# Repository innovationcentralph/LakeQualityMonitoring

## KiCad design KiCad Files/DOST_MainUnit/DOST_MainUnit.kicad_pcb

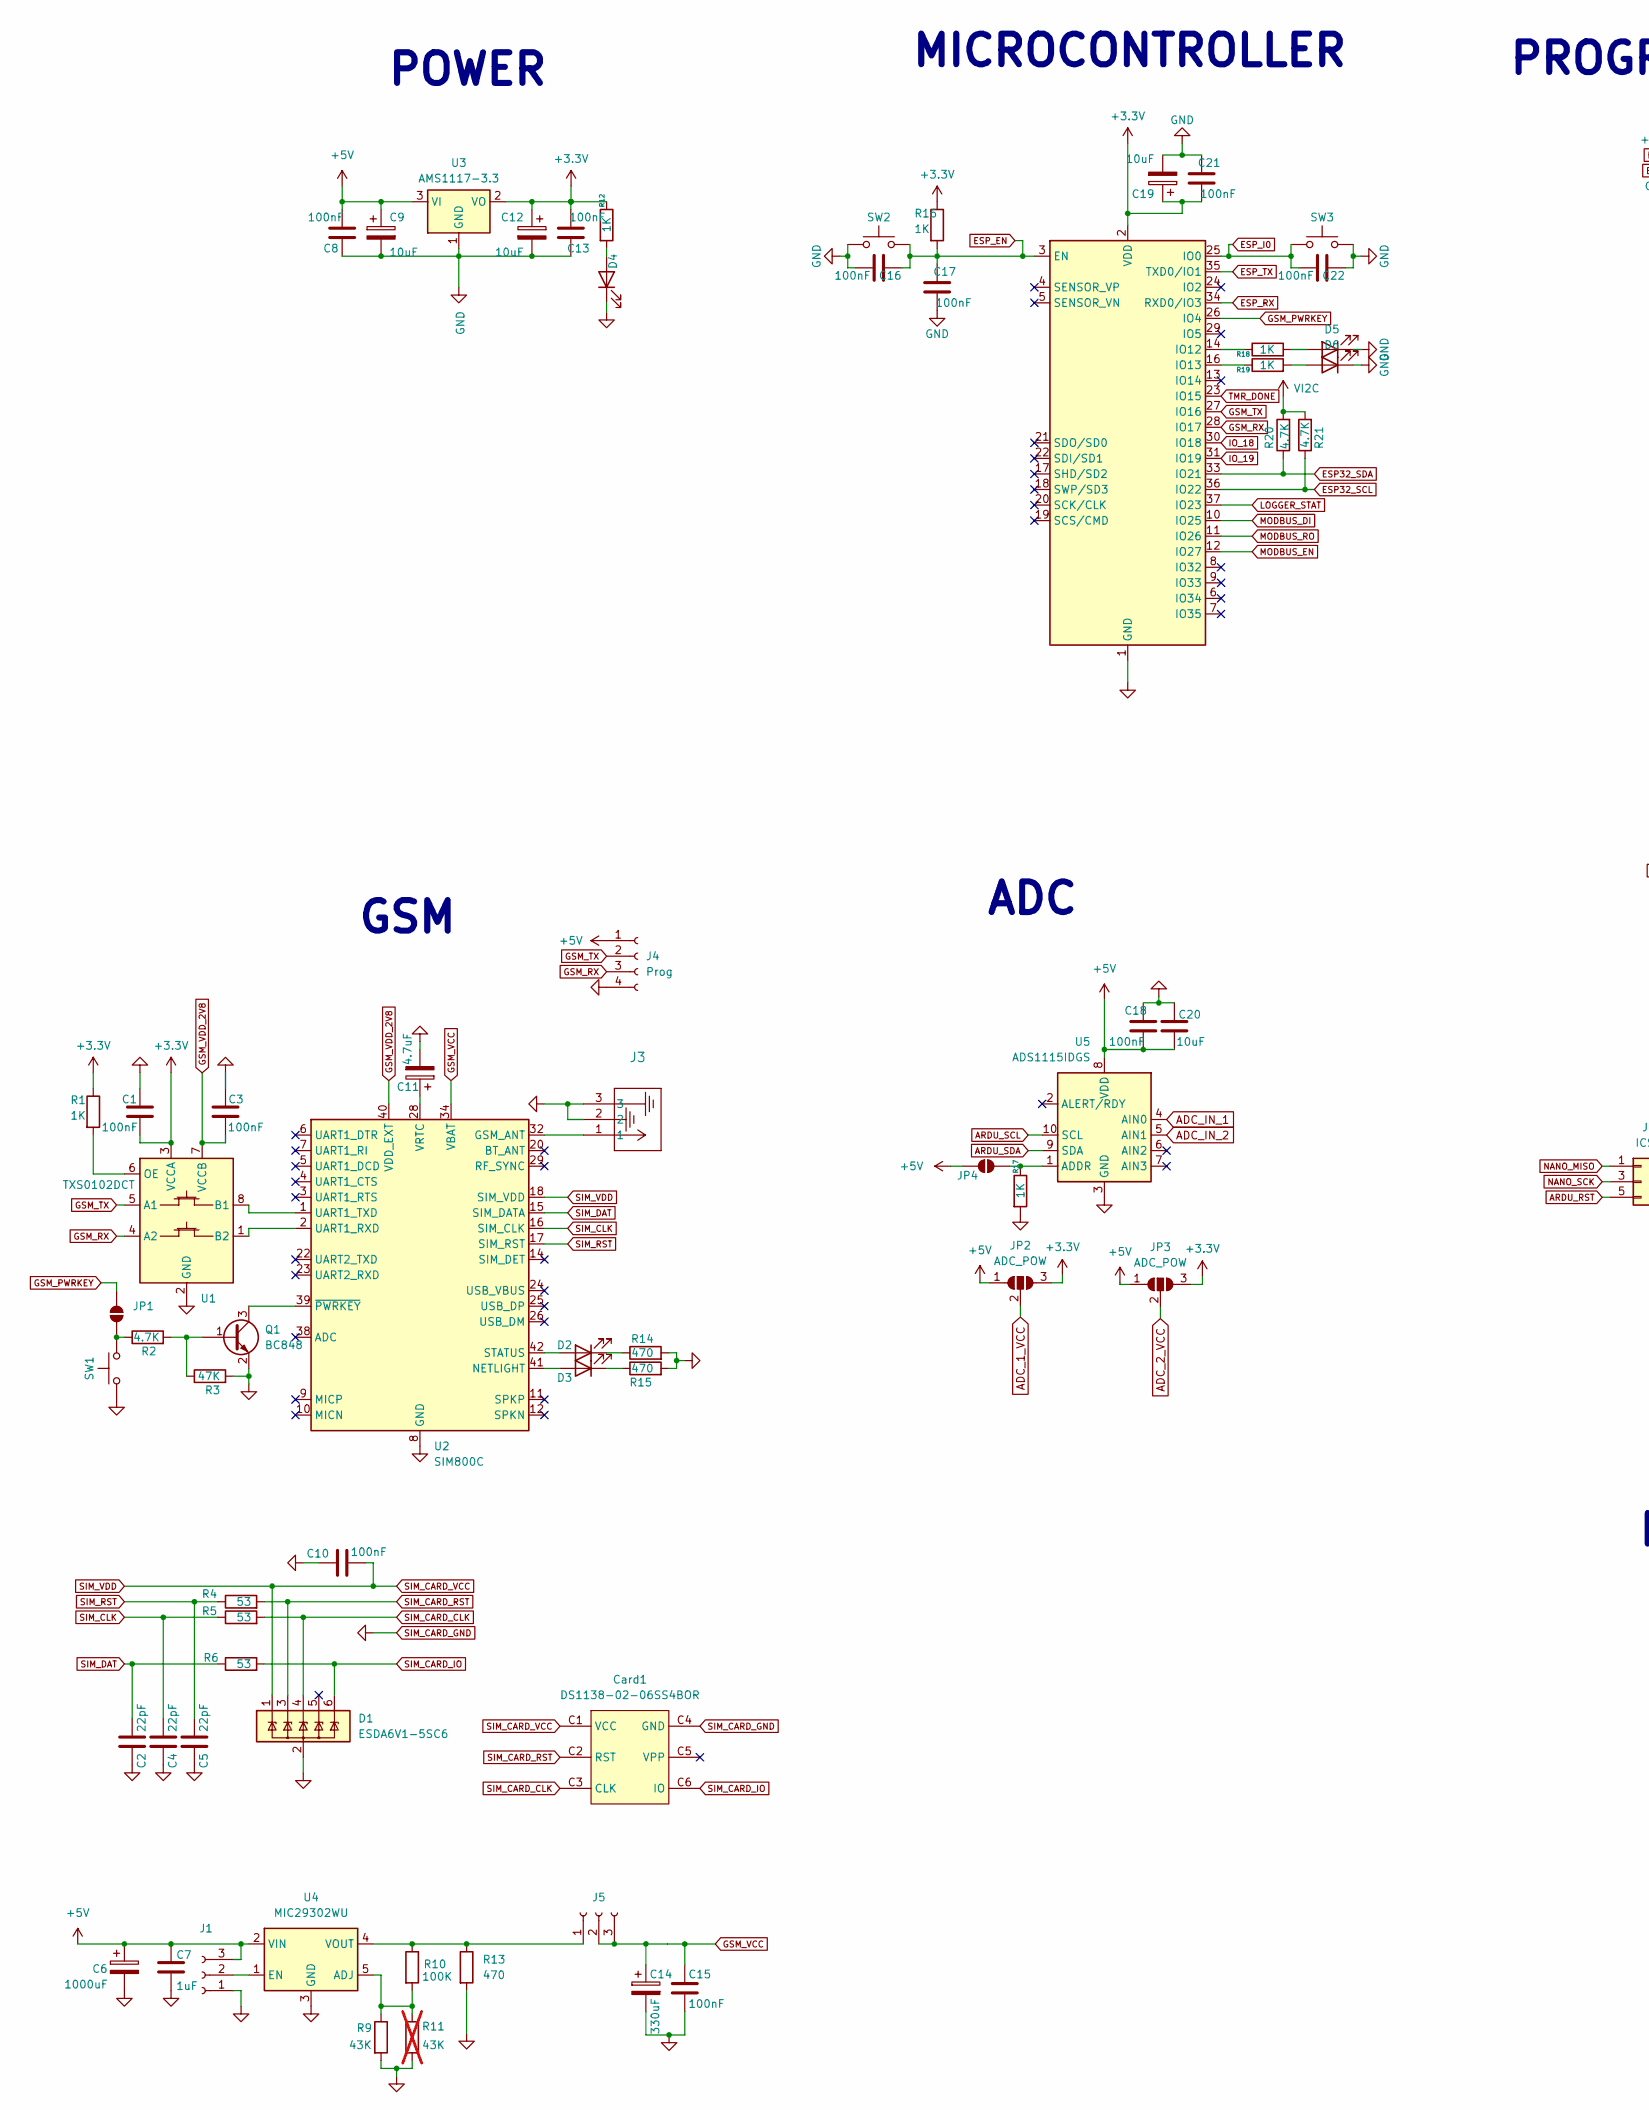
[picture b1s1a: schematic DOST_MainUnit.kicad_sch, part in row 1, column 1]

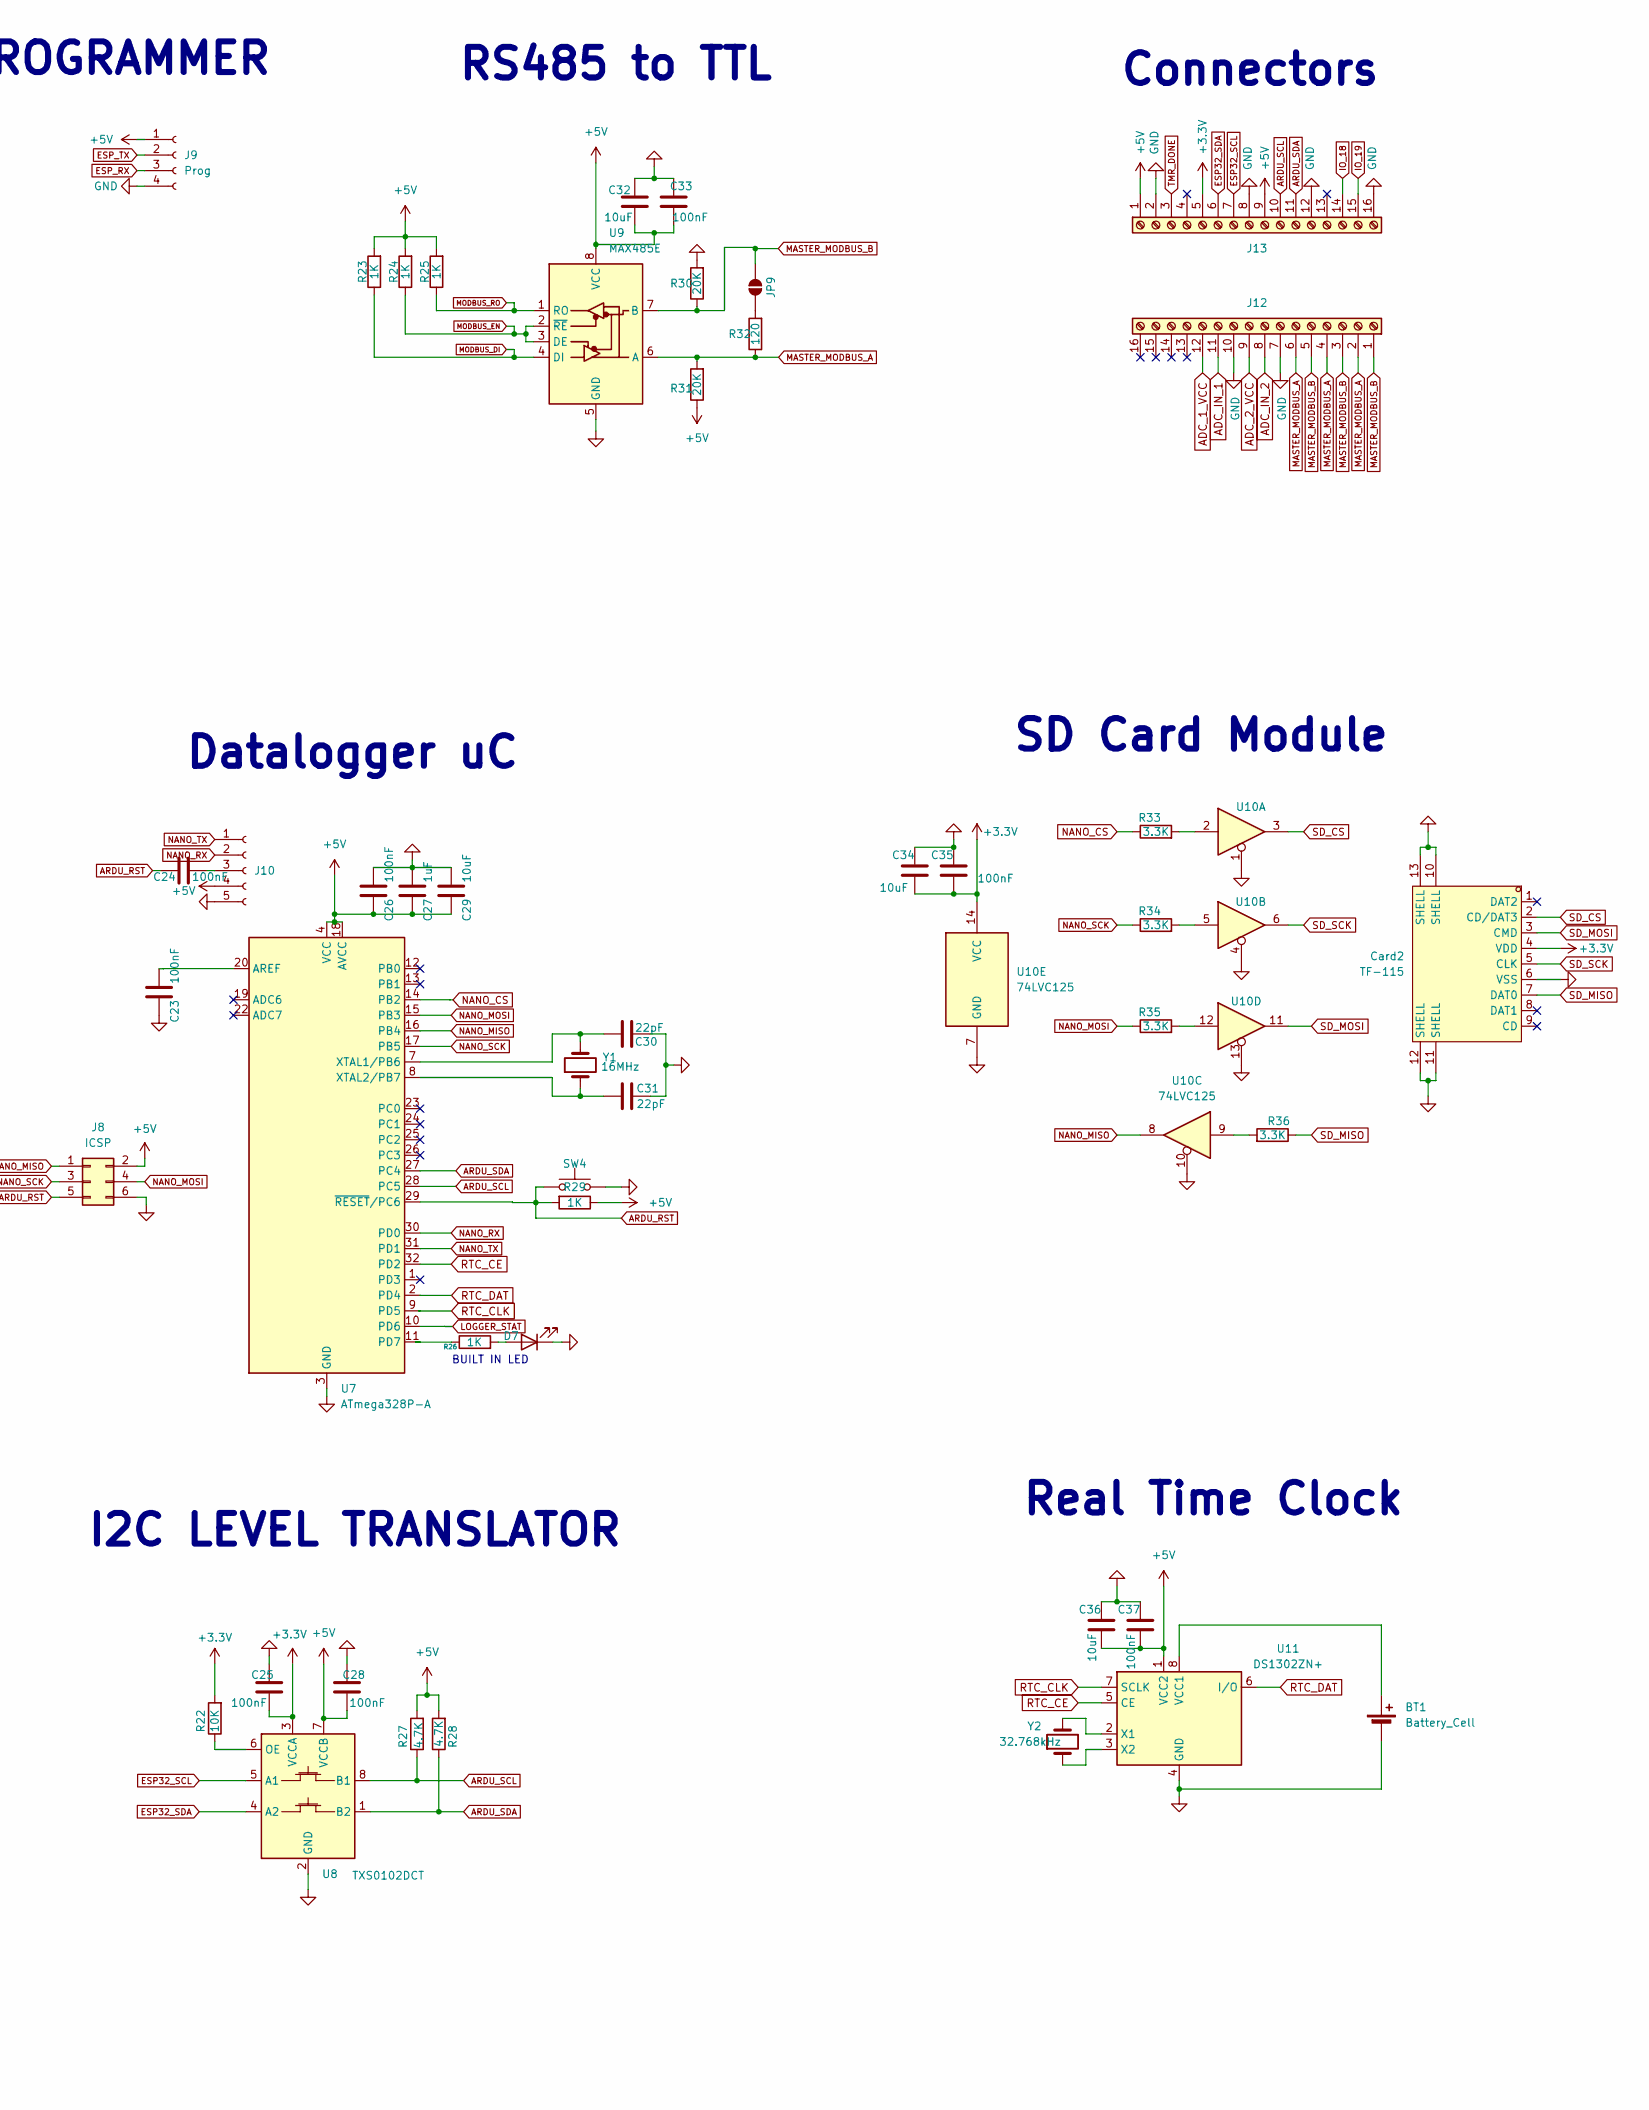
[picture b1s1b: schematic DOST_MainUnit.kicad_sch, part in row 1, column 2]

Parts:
BT1: Battery_Cell; BAT-TH_CR2032-BS-6-1; LCSC C70377
C1, C3, C25, C28: 100nF; C_0805_2012Metric_Pad1.18x1.45mm_HandSolder; LCSC C1546
C2, C4, C5: 22pF; C_0805_2012Metric_Pad1.18x1.45mm_HandSolder
C6: 1000uF; CP_Elec_10x10.5
C7: 1uF; C_0805_2012Metric_Pad1.18x1.45mm_HandSolder
C8, C13, C16, C17, C18, C21, C22, C23, C24, C26, C33, C35, C37: 100nF; C_0805_2012Metric_Pad1.18x1.45mm_HandSolder; LCSC C60474
C9, C12, C19, C32: 10uF; C_0805_2012Metric_Pad1.18x1.45mm_HandSolder; LCSC C15850
C10, C15: 100nF; C_0805_2012Metric_Pad1.18x1.45mm_HandSolder
C11: 4.7uF; CP_EIA-3528-12_Kemet-T_Pad1.50x2.35mm_HandSolder
C14: 330uF; CP_EIA-7343-31_Kemet-D_Pad2.25x2.55mm_HandSolder
C20, C29, C34, C36: 10uF; C_0805_2012Metric_Pad1.18x1.45mm_HandSolder; LCSC C96446
C27: 1uF; C_0805_2012Metric_Pad1.18x1.45mm_HandSolder; LCSC C52923
C30, C31: 22pF; C_0805_2012Metric_Pad1.18x1.45mm_HandSolder; LCSC C96446
Card1: DS1138-02-06SS4BOR; SIM-SMD_DS1138-02-06SS4BOR; LCSC Part C91413
Card2: TF-115; TF-SMD_TF-115; LCSC C266620
D1: ESDA6V1-5SC6; SOT-23-6
D2, D3: LED; LED_0805_2012Metric_Pad1.15x1.40mm_HandSolder
D4, D5, D6, D7: LED; LED_0805_2012Metric_Pad1.15x1.40mm_HandSolder; LCSC C2297
J1, J5: Conn_01x03_Socket; PinHeader_1x03_P2.54mm_Vertical
J3: CONUFL001-SMD-T; CONN1_CONUFL_TEC
J4, J9: Prog; PinHeader_1x04_P2.54mm_Vertical
J8: ICSP; PinHeader_2x03_P2.54mm_Vertical_SMD
J10: Conn_01x05_Socket; PinHeader_1x05_P2.54mm_Vertical
J12, J13: Screw_Terminal_01x16; TerminalBlock_Phoenix_MKDS-1,5-16-5.08_1x16_P5.08mm_Horizon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
JP1, JP4, JP9: SolderJumper_2_Open; SolderJumper-2_P1.3mm_Open_Pad1.0x1.5mm
JP2, JP3: ADC_POW; SolderJumper-3_P1.3mm_Open_Pad1.0x1.5mm
Q1: BC848; SOT-23
R1, R12, R16, R17, R18, R19, R23, R24, R25, R26, R29: 1K; R_0603_1608Metric_Pad0.98x0.95mm_HandSolder; LCSC C21190
R2: 4.7K; R_0603_1608Metric_Pad0.98x0.95mm_HandSolder
R3: 47K; R_0805_2012Metric_Pad1.20x1.40mm_HandSolder
R4, R5, R6: 53; R_0805_2012Metric_Pad1.20x1.40mm_HandSolder
R9: 43K; R_0805_2012Metric_Pad1.20x1.40mm_HandSolder
R10: 100K; R_0805_2012Metric_Pad1.20x1.40mm_HandSolder
R11: 43K; R_0805_2012Metric_Pad1.20x1.40mm_HandSolder; not fitted
R13, R14, R15: 470; R_0805_2012Metric_Pad1.20x1.40mm_HandSolder
R20, R21, R27, R28: 4.7K; R_0603_1608Metric_Pad0.98x0.95mm_HandSolder; LCSC C23162
R22: 10K; R_0603_1608Metric_Pad0.98x0.95mm_HandSolder; LCSC C25804
R30, R31: 20K; R_0805_2012Metric_Pad1.20x1.40mm_HandSolder; LCSC C163978
R32: 120; R_0805_2012Metric_Pad1.20x1.40mm_HandSolder; LCSC C2907224
R33, R34, R35, R36: 3.3K; R_0603_1608Metric_Pad0.98x0.95mm_HandSolder; LCSC C22978
SW1, SW2, SW3, SW4: SW_Push; SW_SPST_CK_RS282G05A3; LCSC C2689642
U1, U8: TXS0102DCT; SSOP-8_2.95x2.8mm_P0.65mm
U2: SIM800C; SIMCom_SIM800C
U3: AMS1117-3.3; SOT-223-3_TabPin2
U4: MIC29302WU; TO-263-5_TabPin3
U5: ADS1115IDGS; VSSOP-10_3x3mm_P0.5mm; LCSC C37593
U6: ESP32-WROOM-32; LCSC C529577
U7: ATmega328P-A; TQFP-32_7x7mm_P0.8mm; LCSC C14877
U9: MAX485E; SOP-8_3.9x4.9mm_P1.27mm; LCSC C481667
U10: 74LVC125; TSSOP-14_L5.0-W4.4-P0.65-LS6.4-BL; LCSC C6059
U11: DS1302ZN+; SOIC-8_3.9x4.9mm_P1.27mm; LCSC C14334
Y1: 16MHz; Crystal_HC49-4H_Vertical
Y2: 32.768kHz; Crystal_C38-LF_D3.0mm_L8.0mm_Vertical; LCSC C97606

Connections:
+3.3V: C1.2, C12.1, C13.1, C19.1, C21.1, C25.2, C34.1, C35.1, Card2.4 (VDD), J13.5, JP2.3 (B), JP3.3 (B), R1.1, R12.1, R16.1, R22.2, U1.3 (VCCA), U3.2 (VO), U6.2 (VDD), U8.3 (VCCA), U10.14 (VCC)
+5V: C6.1, C7.1, C8.1, C9.1, C18.1, C20.2, C26.2, C27.2, C28.2, C29.2, C32.2, C33.1, C36.1, C37.1, J1.3, J4.1, J8.2, J9.1, J10.4, J13.1, J13.9, JP2.1 (A), JP3.1 (A), JP4.2 (B), R23.2, R24.2, R25.2, R27.2, R28.2, R29.1, R31.1, U3.3 (VI), U4.2 (VIN), U5.8 (VDD), U7.4 (VCC), U7.6 (VCC), U7.18 (AVCC), U8.7 (VCCB), U9.8 (VCC), U11.1 (VCC2)
ADC_1_VCC: J12.12, JP2.2 (C)
ADC_2_VCC: J12.9, JP3.2 (C)
ADC_IN_1: J12.11, U5.4 (AIN0)
ADC_IN_2: J12.8, U5.5 (AIN1)
ARDU_RST: C24.2, J8.5, R29.2, SW4.1, U7.29 (~RESET/PC6)
ARDU_SCL: J13.10, R27.1, U5.10 (SCL), U7.28 (PC5), U8.8 (B1)
ARDU_SDA: J13.11, R28.1, U5.9 (SDA), U7.27 (PC4), U8.1 (B2)
ESP32_SCL: J13.7, R21.1, U6.36 (IO22), U8.5 (A1)
ESP32_SDA: J13.6, R20.1, U6.33 (IO21), U8.4 (A2)
ESP_EN: C16.2, C17.2, R16.2, SW2.2, U6.3 (EN)
ESP_I0: C22.1, SW3.1, U6.25 (IO0)
ESP_RX: J9.3, U6.34 (RXD0/IO3)
ESP_TX: J9.2, U6.35 (TXD0/IO1)
GSM_PWRKEY: JP1.2 (B), U6.26 (IO4)
GSM_RX: J4.3, U1.4 (A2), U6.28 (IO17)
GSM_TX: J4.2, U1.5 (A1), U6.27 (IO16)
GSM_VCC: C14.1, C15.1, J5.2, J5.3, U2.34 (VBAT), U2.35 (VBAT)
GSM_VDD_2V8: C3.2, U1.7 (VCCB), U2.40 (VDD_EXT)
IO_18: J13.14, U6.30 (IO18)
IO_19: J13.15, U6.31 (IO19)
LOGGER_STAT: U6.37 (IO23), U7.10 (PD6)
MASTER_MODBUS_A: J12.2, J12.4, J12.6, R31.2, R32.1, U9.6 (A)
MASTER_MODBUS_B: J12.1, J12.3, J12.5, JP9.2 (B), R30.1, U9.7 (B)
MODBUS_DI: R23.1, U6.10 (IO25), U9.4 (DI)
MODBUS_EN: R24.1, U6.12 (IO27), U9.2 (~RE), U9.3 (DE)
MODBUS_RO: R25.1, U6.11 (IO26), U9.1 (RO)
NANO_CS: R33.1, U7.14 (PB2)
NANO_MISO: J8.1, U7.16 (PB4), U10.8
NANO_MOSI: J8.4, R35.1, U7.15 (PB3)
NANO_RX: J10.2, U7.30 (PD0)
NANO_SCK: J8.3, R34.1, U7.17 (PB5)
NANO_TX: J10.1, U7.31 (PD1)
unnamed: BT1.1 (+), U11.8 (VCC1)
unnamed: D2.2 (A), U2.42 (STATUS)
unnamed: D2.1 (K), R14.1
unnamed: D3.2 (A), U2.41 (NETLIGHT)
unnamed: D3.1 (K), R15.1
unnamed: D4.2 (A), R12.2
unnamed: D5.2 (A), R18.2
unnamed: D6.2 (A), R19.2
unnamed: D7.2 (A), R26.2
unnamed: J1.2, U4.1 (EN)
unnamed: J5.1, R10.1, R13.1, U4.4 (VOUT)
unnamed: C24.1, J10.3
unnamed: JP1.1 (A), R2.1, SW1.2
unnamed: JP4.1 (A), R17.1, U5.1 (ADDR)
unnamed: JP9.1 (A), R32.2
unnamed: Q1.1 (B), R2.2, R3.1
unnamed: Q1.3 (C), U2.39 (~PWRKEY)
unnamed: R33.2, U10.2
unnamed: R34.2, U10.5
unnamed: R35.2, U10.12
unnamed: R36.2, U10.9
unnamed: U1.8 (B1), U2.1 (UART1_TXD)
unnamed: U1.1 (B2), U2.2 (UART1_RXD)
unnamed: R1.2, U1.6 (OE)
unnamed: J3.1, U2.32 (GSM_ANT)
unnamed: C11.1, U2.28 (VRTC)
unnamed: R9.1, R10.2, R11.1, U4.5 (ADJ)
unnamed: R18.1, U6.14 (IO12)
unnamed: R19.1, U6.16 (IO13)
unnamed: C23.1, U7.20 (AREF)
unnamed: R26.1, U7.11 (PD7)
unnamed: C30.1, U7.7 (XTAL1/PB6), Y1.2
unnamed: C31.1, U7.8 (XTAL2/PB7), Y1.1
unnamed: R22.1, U8.6 (OE)
unnamed: U11.2 (X1), Y2.2
unnamed: U11.3 (X2), Y2.1
RTC_CE: U7.32 (PD2), U11.5 (CE)
RTC_CLK: U7.9 (PD5), U11.7 (SCLK)
RTC_DAT: U7.2 (PD4), U11.6 (I/O)
SD_CS: Card2.2 (CD/DAT3), U10.3
SD_MISO: Card2.7 (DAT0), R36.1
SD_MOSI: Card2.3 (CMD), U10.11
SD_SCK: Card2.5 (CLK), U10.6
SIM_CARD_CLK: Card1.C3 (CLK), D1.4 (IO3), R5.2
SIM_CARD_GND: BT1.2 (-), C1.1, C2.1, C3.1, C4.1, C5.1, C6.2, C7.2, C8.2, C9.2, C10.1, C11.2, C12.2, C13.2, C14.2, C15.2, C16.1, C17.1, C18.2, C19.2, C20.1, C21.2, C22.2, C23.2, C25.1, C26.1, C27.1, C28.1, C29.1, C30.2, C31.2, C32.1, C33.2, C34.2, C35.2, C36.2, C37.2, Card1.C4 (GND), Card2.6 (VSS), Card2.10 (SHELL), Card2.11 (SHELL), Card2.12 (SHELL), Card2.13 (SHELL), D1.2 (GND), D4.1 (K), D5.1 (K), D6.1 (K), D7.1 (K), J1.1, J3.2, J3.3, J4.4, J8.6, J9.4, J10.5, J12.7, J12.10, J13.2, J13.8, J13.12, J13.16, Q1.2 (E), R3.2, R9.2, R11.2, R13.2, R14.2, R15.2, R17.2, R30.2, SW1.1, SW2.1, SW3.2, SW4.2, U1.2 (GND), U2.8 (GND), U2.13 (GND), U2.19 (GND), U2.21 (GND), U2.27 (GND), U2.30 (GND), U2.31 (GND), U2.33 (GND), U2.36 (GND), U2.37 (GND), U3.1 (GND), U4.3 (GND), U5.3 (GND), U6.1 (GND), U6.15 (GND), U6.38 (GND), U6.39 (GND), U7.3 (GND), U7.5 (GND), U7.21 (GND), U8.2 (GND), U9.5 (GND), U10.1, U10.4, U10.7 (GND), U10.10, U10.13, U11.4 (GND)
SIM_CARD_IO: Card1.C6 (IO), D1.6 (IO5), R6.2
SIM_CARD_RST: Card1.C2 (RST), D1.3 (IO2), R4.2
SIM_CARD_VCC: C10.2, Card1.C1 (VCC), D1.1 (IO1), U2.18 (SIM_VDD)
SIM_CLK: C4.2, R5.1, U2.16 (SIM_CLK)
SIM_DAT: C2.2, R6.1, U2.15 (SIM_DATA)
SIM_RST: C5.2, R4.1, U2.17 (SIM_RST)
TMR_DONE: J13.3, U6.23 (IO15)
VI2C: R20.2, R21.2

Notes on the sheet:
Datalogger uC
RS485 to TTL
SD Card Module
GSM
I2C LEVEL TRANSLATOR
Connectors
POWER
MICROCONTROLLER
Real Time Clock
BUILT IN LED
PROGRAMMER
ADC

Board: 2 copper layers, 113 parts (1 on the bottom side), 87 nets, no tracks yet.

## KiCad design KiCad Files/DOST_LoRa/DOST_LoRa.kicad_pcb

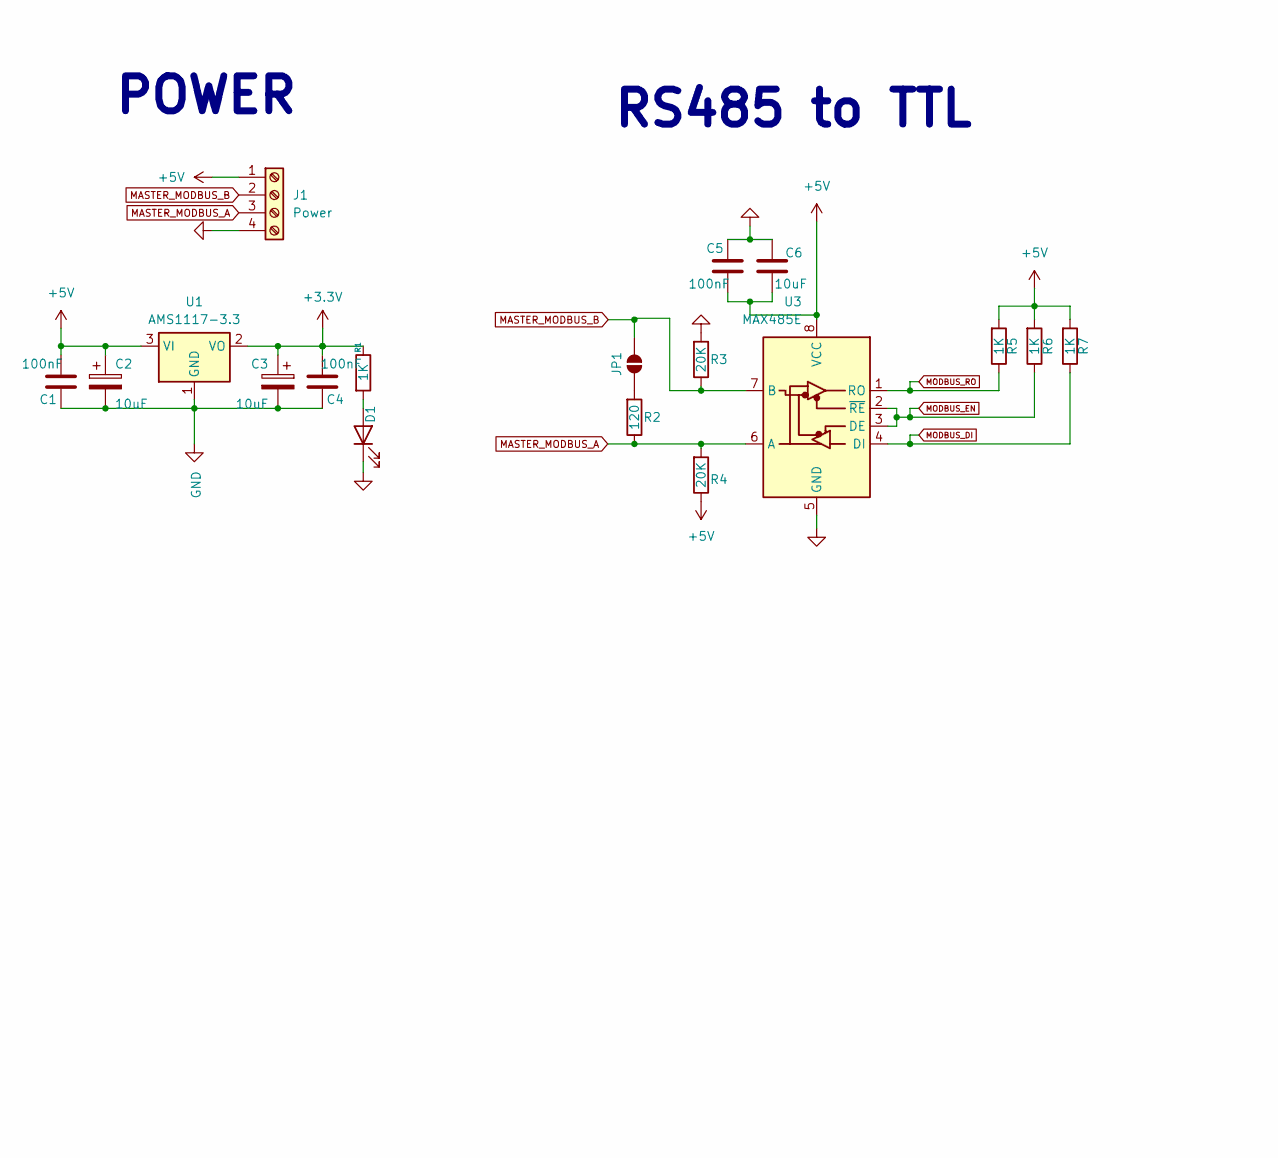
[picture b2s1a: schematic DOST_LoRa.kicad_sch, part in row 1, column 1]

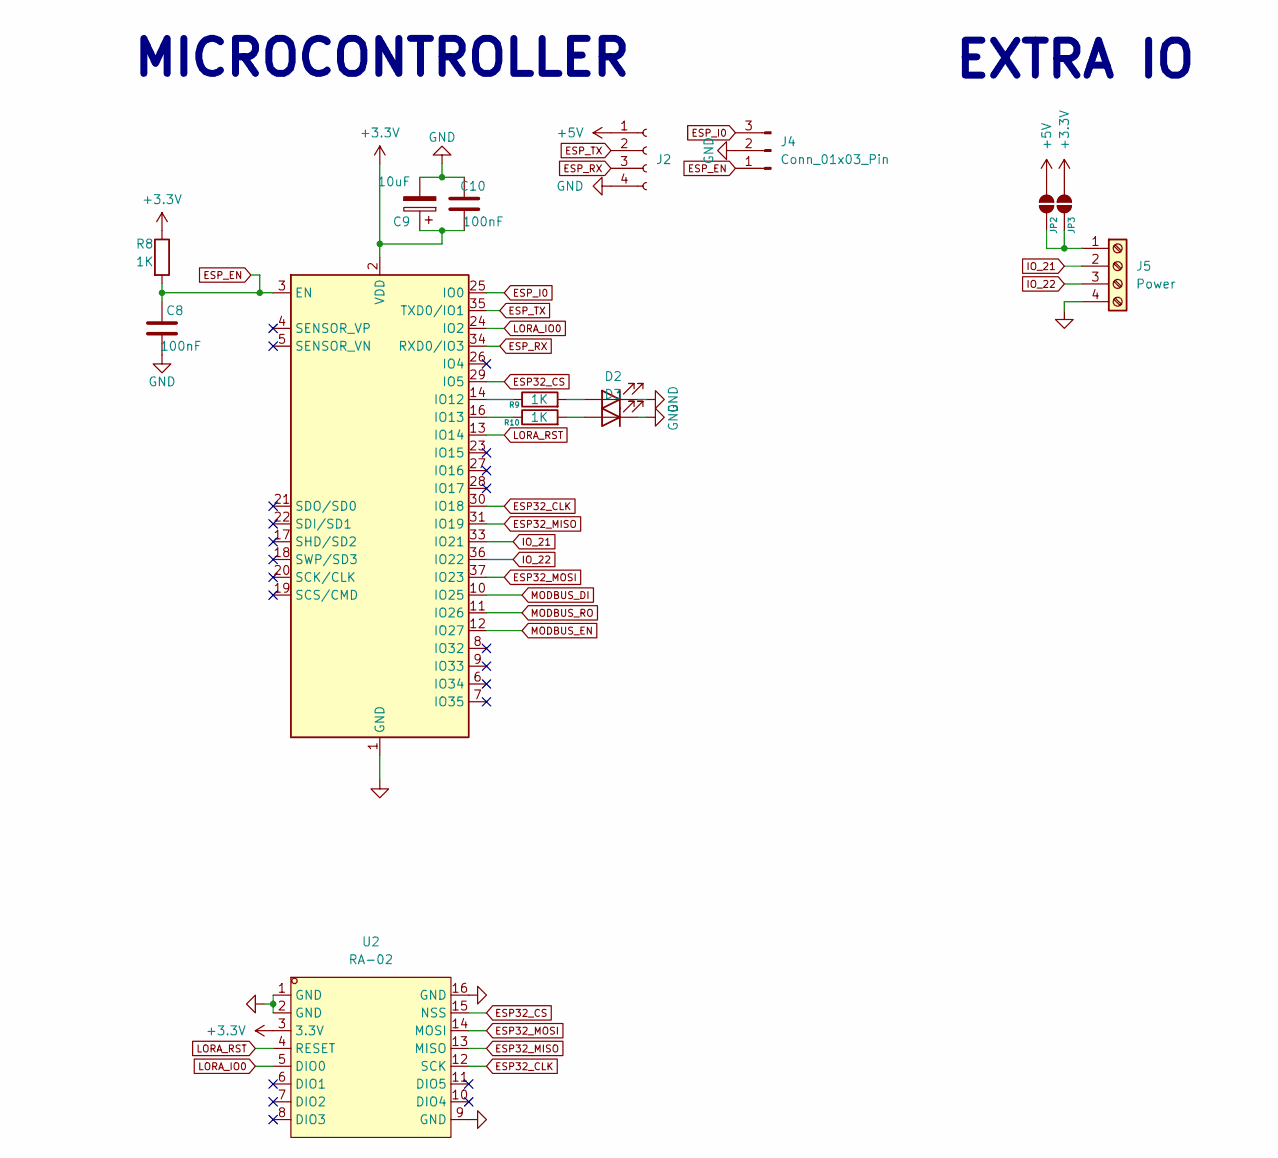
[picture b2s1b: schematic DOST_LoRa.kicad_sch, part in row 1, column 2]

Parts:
C1, C4, C5, C8, C10: 100nF; C_0805_2012Metric_Pad1.18x1.45mm_HandSolder; LCSC C60474
C2, C3, C6, C9: 10uF; C_0805_2012Metric_Pad1.18x1.45mm_HandSolder; LCSC C15850
D1, D2, D3: LED; LED_0805_2012Metric_Pad1.15x1.40mm_HandSolder; LCSC C2297
J1, J5: Power; TerminalBlock_Phoenix_MKDS-1,5-4-5.08_1x04_P5.08mm_Horizont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
J2: PinHeader_1x04_P2.54mm_Vertical
J4: Conn_01x03_Pin; PinHeader_1x03_P2.54mm_Vertical
JP1, JP2, JP3: SolderJumper_2_Open; SolderJumper-2_P1.3mm_Open_Pad1.0x1.5mm
R1, R5, R6, R7, R8, R9, R10: 1K; R_0603_1608Metric_Pad0.98x0.95mm_HandSolder; LCSC C21190
R2: 120; R_0805_2012Metric_Pad1.20x1.40mm_HandSolder; LCSC C2907224
R3, R4: 20K; R_0805_2012Metric_Pad1.20x1.40mm_HandSolder; LCSC C163978
U1: AMS1117-3.3; SOT-223-3_TabPin2
U2: RA-02; WIRELM-SMD_RA-02-BL; LCSC Part C90039
U3: MAX485E; SOP-8_3.9x4.9mm_P1.27mm; LCSC C481667
U4: ESP32-WROOM-32; ESP32-WROOM-32U; LCSC C529577

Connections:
+3.3V: C3.1, C4.1, C9.1, C10.1, JP3.2 (B), R1.1, R8.1, U1.2 (VO), U2.3 (3.3V), U4.2 (VDD)
+5V: C1.1, C2.1, C5.1, C6.2, J1.1, J2.1, JP2.2 (B), R4.1, R5.2, R6.2, R7.2, U1.3 (VI), U3.8 (VCC)
ESP32_CLK: U2.12 (SCK), U4.30 (IO18)
ESP32_CS: U2.15 (NSS), U4.29 (IO5)
ESP32_MISO: U2.13 (MISO), U4.31 (IO19)
ESP32_MOSI: U2.14 (MOSI), U4.37 (IO23)
ESP_EN: C8.2, J4.1, R8.2, U4.3 (EN)
ESP_I0: J4.3, U4.25 (IO0)
ESP_RX: J2.3, U4.34 (RXD0/IO3)
ESP_TX: J2.2, U4.35 (TXD0/IO1)
GND: C1.2, C2.2, C3.2, C4.2, C5.2, C6.1, C8.1, C9.2, C10.2, D1.1 (K), D2.1 (K), D3.1 (K), J1.4, J2.4, J4.2, J5.4, R3.2, U1.1 (GND), U2.1 (GND), U2.2 (GND), U2.9 (GND), U2.16 (GND), U3.5 (GND), U4.1 (GND), U4.15 (GND), U4.38 (GND), U4.39 (GND)
IO_21: J5.2, U4.33 (IO21)
IO_22: J5.3, U4.36 (IO22)
LORA_IO0: U2.5 (DIO0), U4.24 (IO2)
LORA_RST: U2.4 (RESET), U4.13 (IO14)
MASTER_MODBUS_A: J1.3, R2.1, R4.2, U3.6 (A)
MASTER_MODBUS_B: J1.2, JP1.2 (B), R3.1, U3.7 (B)
MODBUS_DI: R7.1, U3.4 (DI), U4.10 (IO25)
MODBUS_EN: R6.1, U3.2 (~RE), U3.3 (DE), U4.12 (IO27)
MODBUS_RO: R5.1, U3.1 (RO), U4.11 (IO26)
unnamed: D1.2 (A), R1.2
unnamed: D2.2 (A), R9.2
unnamed: D3.2 (A), R10.2
unnamed: J5.1, JP2.1 (A), JP3.1 (A)
unnamed: JP1.1 (A), R2.2
unnamed: R9.1, U4.14 (IO12)
unnamed: R10.1, U4.16 (IO13)

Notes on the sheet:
EXTRA IO
POWER
MICROCONTROLLER
RS485 to TTL

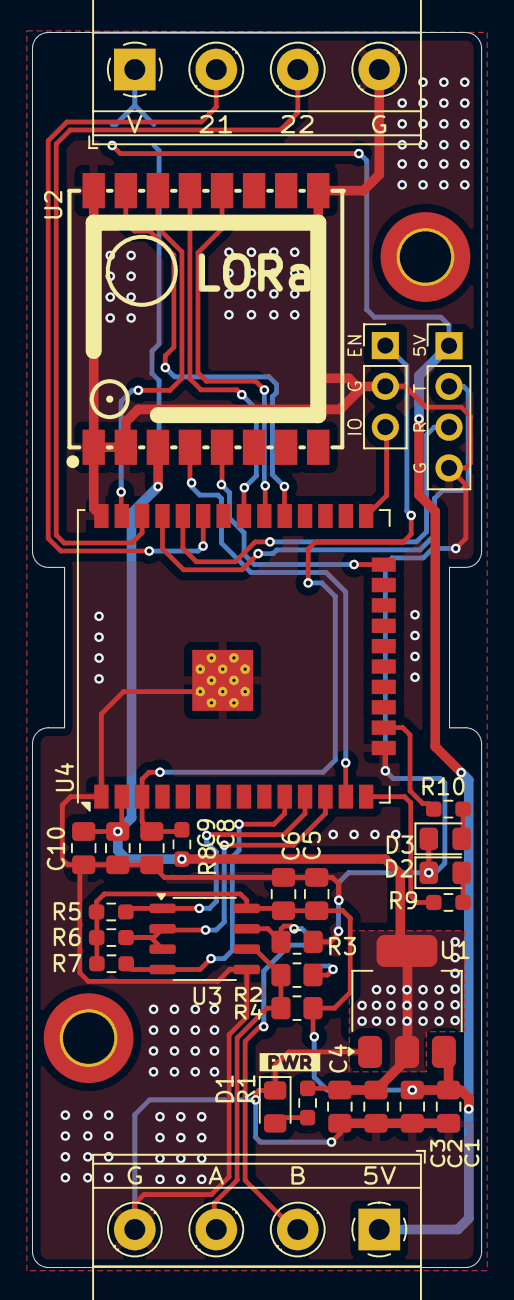
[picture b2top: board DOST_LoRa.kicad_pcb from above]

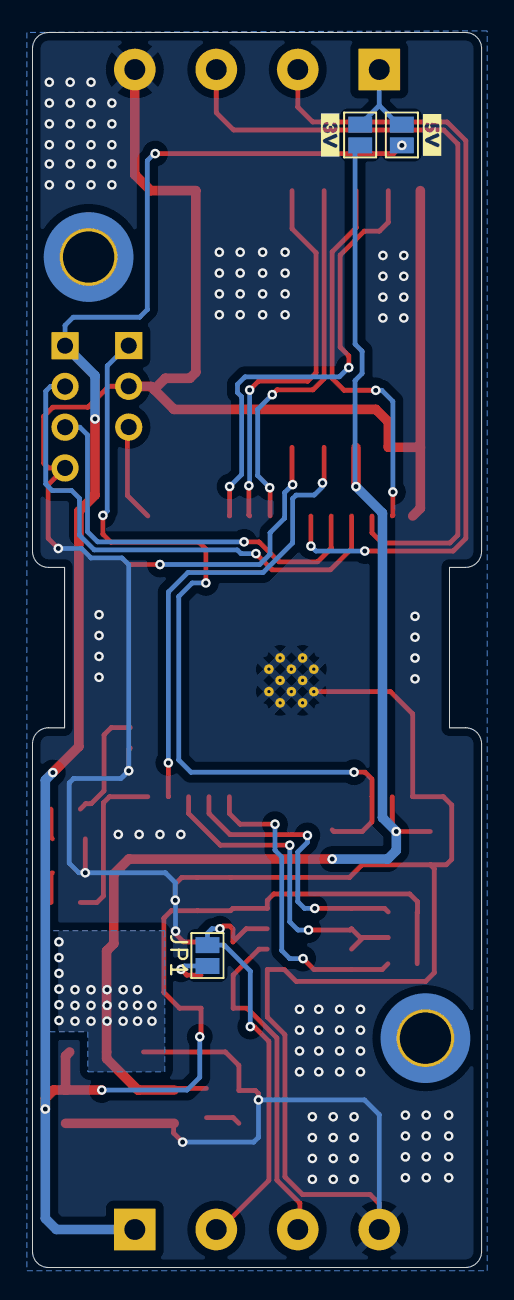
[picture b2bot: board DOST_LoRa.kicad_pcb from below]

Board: 2 copper layers, 28.0 x 77.0 mm, 36 parts (5 on the bottom side), 27 nets.

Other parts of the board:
kibuzzard-6783FC2A: G***; kibuzzard-6783FC2A
kibuzzard-6783FC31: G***; kibuzzard-6783FC31
kibuzzard-6783FECC: G***; kibuzzard-6783FECC

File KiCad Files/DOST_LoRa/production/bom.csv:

Designator,Footprint,Quantity,Value,LCSC Part #
"C1, C10, C4, C5, C8",0805,5,100nF, C60474
"C2, C3, C6, C9",0805,4,10uF,C15850
"D1, D2, D3",0805,3,LED,C2297
"J1, J5","TerminalBlock_Phoenix_MKDS-1,5-4-5.08_1x04_P5.08mm_Horizontal",2,Power,
J2,PinHeader_1x04_P2.54mm_Vertical,1,~,
J4,PinHeader_1x03_P2.54mm_Vertical,1,Conn_01x03_Pin,
"R1, R10, R5, R6, R7, R8, R9",0603,7,1K,C21190
R2,0805,1,120,C2907224
"R3, R4",0805,2,20K,C163978
U1,SOT-223-3_TabPin2,1,AMS1117-3.3,
U2,WIRELM-SMD_RA-02-BL,1,RA-02,C90039
U3,SOP-8_3.9x4.9mm_P1.27mm,1,MAX485E,C481667
U4,ESP32-WROOM-32U,1,ESP32-WROOM-32,C529577

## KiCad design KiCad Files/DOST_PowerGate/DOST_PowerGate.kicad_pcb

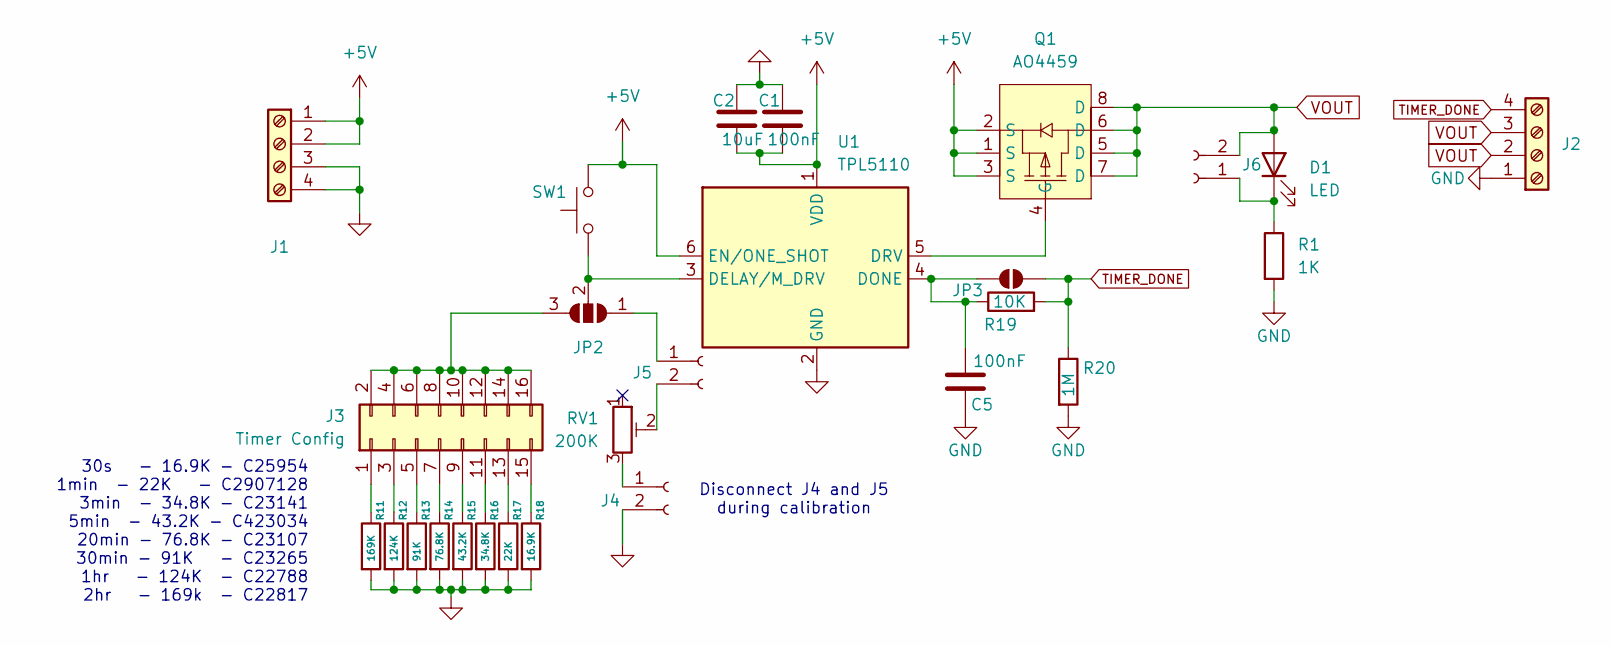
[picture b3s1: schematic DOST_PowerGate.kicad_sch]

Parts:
C1: 100nF; C_0805_2012Metric_Pad1.18x1.45mm_HandSolder
C2: 10uF; C_0805_2012Metric_Pad1.18x1.45mm_HandSolder
C5: 100nF; C_0805_2012Metric_Pad1.18x1.45mm_HandSolder; LCSC C60474
D1: LED; LED_0805_2012Metric_Pad1.15x1.40mm_HandSolder
J1, J2: Screw_Terminal_01x04; TerminalBlock_Phoenix_MKDS-1,5-4-5.08_1x04_P5.08mm_Horizont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
J3: Timer Config; PinHeader_2x08_P2.54mm_Vertical
J4, J5, J6: Conn_01x02_Socket; PinHeader_1x02_P2.54mm_Vertical
JP2: SolderJumper_3_Open; SolderJumper-3_P1.3mm_Open_Pad1.0x1.5mm
JP3: SolderJumper_2_Open; SolderJumper-2_P1.3mm_Open_Pad1.0x1.5mm
Q1: AO4459; SOP-8_L5.0-W4.0-P1.27-LS6.2-BL; LCSC Part C49047
R1: 1K; R_0603_1608Metric_Pad0.98x0.95mm_HandSolder
R11: 169K; R_0805_2012Metric_Pad1.20x1.40mm_HandSolder; LCSC C22817
R12: 124K; R_0805_2012Metric_Pad1.20x1.40mm_HandSolder; LCSC C22788
R13: 91K; R_0805_2012Metric_Pad1.20x1.40mm_HandSolder; LCSC C23265
R14: 76.8K; R_0805_2012Metric_Pad1.20x1.40mm_HandSolder; LCSC C23107
R15: 43.2K; R_0805_2012Metric_Pad1.20x1.40mm_HandSolder; LCSC C423034
R16: 34.8K; R_0805_2012Metric_Pad1.20x1.40mm_HandSolder; LCSC C23141
R17: 22K; R_0805_2012Metric_Pad1.20x1.40mm_HandSolder; LCSC C2907128
R18: 16.9K; R_0805_2012Metric_Pad1.20x1.40mm_HandSolder; LCSC C25954
R19: 10K; R_0603_1608Metric_Pad0.98x0.95mm_HandSolder; LCSC C105578
R20: 1M; R_0805_2012Metric_Pad1.20x1.40mm_HandSolder; LCSC C105578
RV1: 200K; Potentiometer_Bourns_3296W_Vertical
SW1: SW_Push; PinHeader_1x02_P2.54mm_Vertical
U1: TPL5110; SOT-23-6

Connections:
+5V: C1.2, C2.2, J1.1, J1.2, Q1.1 (S), Q1.2 (S), Q1.3 (S), SW1.2, U1.1 (VDD), U1.6 (EN/ONE_SHOT)
GND: C1.1, C2.1, C5.2, J1.3, J1.4, J2.1, J4.2, R1.2, R11.2, R12.2, R13.2, R14.2, R15.2, R16.2, R17.2, R18.2, R20.2, U1.2 (GND)
unnamed: D1.1 (K), J6.1, R1.1
unnamed: J3.1, R11.1
unnamed: J3.3, R12.1
unnamed: J3.5, R13.1
unnamed: J3.7, R14.1
unnamed: J3.9, R15.1
unnamed: J3.2, J3.4, J3.6, J3.8, J3.10, J3.12, J3.14, J3.16, JP2.3 (B)
unnamed: J3.11, R16.1
unnamed: J3.13, R17.1
unnamed: J3.15, R18.1
unnamed: J4.1, RV1.3
unnamed: J5.1, JP2.1 (A)
unnamed: J5.2, RV1.2
unnamed: JP2.2 (C), SW1.1, U1.3 (DELAY/M_DRV)
unnamed: C5.1, JP3.1 (A), R19.1, U1.4 (DONE)
unnamed: Q1.4 (G), U1.5 (DRV)
TIMER_DONE: J2.4, JP3.2 (B), R19.2, R20.1
VOUT: D1.2 (A), J2.2, J2.3, J6.2, Q1.5 (D), Q1.6 (D), Q1.7 (D), Q1.8 (D)

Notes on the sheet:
30s - 16.9K - C25954 1min - 22K - C2907128 3min - 34.8K - C23141 5min - 43.2K - C423034 20min - 76.8K - C23107 30min - 91K - C23265 1hr - 124K - C22788 2hr - 169k - C22817
Disconnect J4 and J5 during calibration

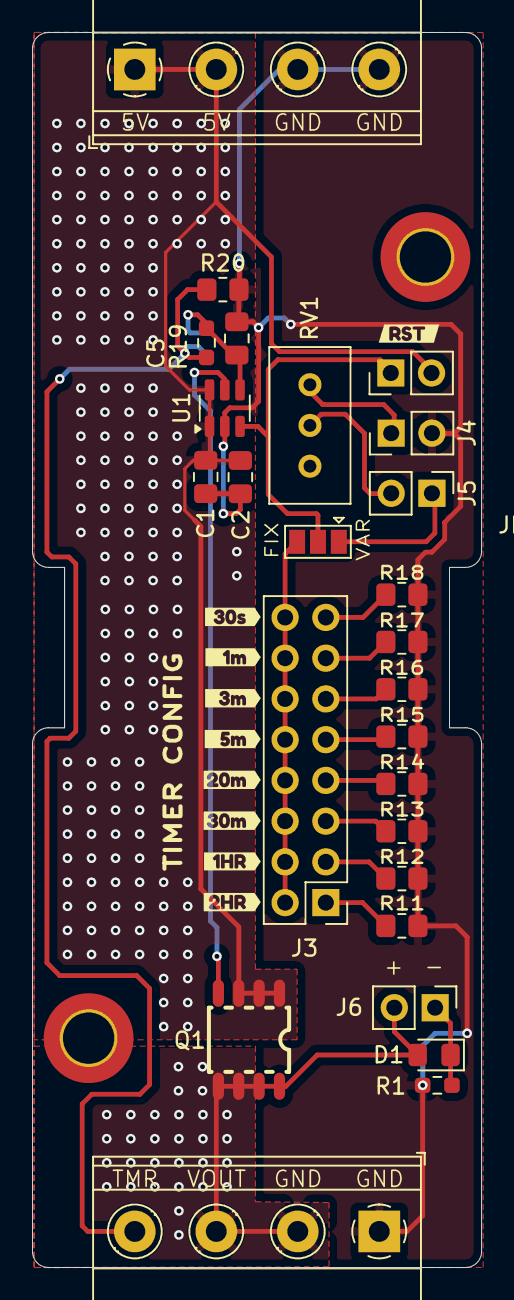
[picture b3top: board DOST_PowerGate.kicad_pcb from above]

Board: 2 copper layers, 28.0 x 77.0 mm, 36 parts (1 on the bottom side), 20 nets.

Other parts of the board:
kibuzzard-678005E5: G***; kibuzzard-678005E5
kibuzzard-678005F6: G***; kibuzzard-678005F6
kibuzzard-6780055F: G***; kibuzzard-6780055F
kibuzzard-6780061E: G***; kibuzzard-6780061E
kibuzzard-6780065B: G***; kibuzzard-6780065B
kibuzzard-6780088B: G***; kibuzzard-6780088B
kibuzzard-67800525: G***; kibuzzard-67800525
kibuzzard-67800635: G***; kibuzzard-67800635
kibuzzard-67800642: G***; kibuzzard-67800642

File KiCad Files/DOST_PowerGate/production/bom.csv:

Designator,Footprint,Quantity,Value,LCSC Part #
C1,0805,1,100nF,
C2,0805,1,10uF,
C5,0805,1,100nF,
D1,0805,1,LED,
"J1, J2","TerminalBlock_Phoenix_MKDS-1,5-4-5.08_1x04_P5.08mm_Horizontal",2,Screw_Terminal_01x04,
J3,PinHeader_2x08_P2.54mm_Vertical,1,Timer Config,
"J4, J5, J6",PinHeader_1x02_P2.54mm_Vertical,3,Conn_01x02_Socket,
Q1,SOP-8_L5.0-W4.0-P1.27-LS6.2-BL,1,AO4459,C49047
R1,0603,1,1K,
R11,0805,1,169K,
R12,0805,1,124K,
R13,0805,1,91K,
R14,0805,1,76.8K,
R15,0805,1,43.2K,
R16,0805,1,34.8K,
R17,0805,1,22K,
R18,0805,1,16.9K,
R19,0603,1,10K,
R20,0805,1,1M,
RV1,Potentiometer_Bourns_3296W_Vertical,1,200K,
SW1,PinHeader_1x02_P2.54mm_Vertical,1,SW_Push,
U1,SOT-23-6,1,TPL5110,

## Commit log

2025-03-04 Initial Commit
    Added Working Firmware
    Sensor Reading
    Lora Sending
    LCD Display Update
    Gateway Code
2025-04-25 Fixed directory for firmware and added hardware files
